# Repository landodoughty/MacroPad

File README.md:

# MacroPad
A Custom Macro Pad I Designed and Built based on the RP2040

# Features:
* Programmable keys allow shortcuts, macros, or controls to be customized.
* Hotswappable MX switches allows you to customize your typing feel.
* RGB Backlighting allows per-key lighting using WS2812/NeoPixel LEDs
* Custom 3d printed case provides a sleek, ergonomic look.

# Building the MacroPad

**The PCB:**
In this repository you can find the raw PCB files and the Gerber files which can allow you to manufacture the PCB through a service such as PCBWay or JLCPCB. I have also attached a BOM containing all the parts for the PCB. Most of the parts utilized on the PCB are very standard, and if you are assembling through JLCPCB the BOM already contains LCSC part numbers for most items. The only items which don't have part numbers, because I did not have them assembled through JLCPCB are the USB Micro-B connector, the reverse mount neopixel LEDs, the MX keyswitch sockets, and a small two pin 2.54mm pitch connector. The USB connector and the two pin connector can be easily bought from many places or even salvaged from old electronics. The [reverse mount LEDs]([url](https://www.adafruit.com/product/4960)) and [MX keyswitch sockets]([url](https://www.adafruit.com/product/4958)) are from adafruit. 

**Switches:**
You can use any MX compatible switches with the PCB, but keep in mind that they all have varying heights. The STLs provided are designed for switches with a 7mm above-board height with DSA keycaps, significantly less than most switches. If you want to use a different heigh you will likely have to adjust the STEP file provided to match your keyheight.

**Code:**
The code is provided but you will need to adjust it to fit your desires. This includes changing the LED modes and key press actions. Currently, the LED modes includes a constant color mode, an RGB mode, and a layer specific mode. To change layers, you press the first two buttons on the top row and then press the third button. To change colors in the constant color mode, you again press the first two buttons on the top row but then press the fourth button to change colors. To change the actions, scroll down to find the section where they are defined. The code shows how to do shortcuts, go to links, make a number pad, and how to create a shift key for a layer. To upload the code for the first time, short the two pins in the 2.54mm connector and then plug the MacroPad in through USB. It should pop up as detected and then yo ucan unshort the pins. Once you have done this once, you should be able to upload just with USB but if you are having issues uploading you may need to repeat the process.

**The Case:**
The case is 3d printed and I have provided both STL and STEP files for your conveinance. This means you can easily customize the case to your liking. The case needs 2 M3 heat set inserts, 2 M3 washers, and 2 M3 x 6 screws to assemble.

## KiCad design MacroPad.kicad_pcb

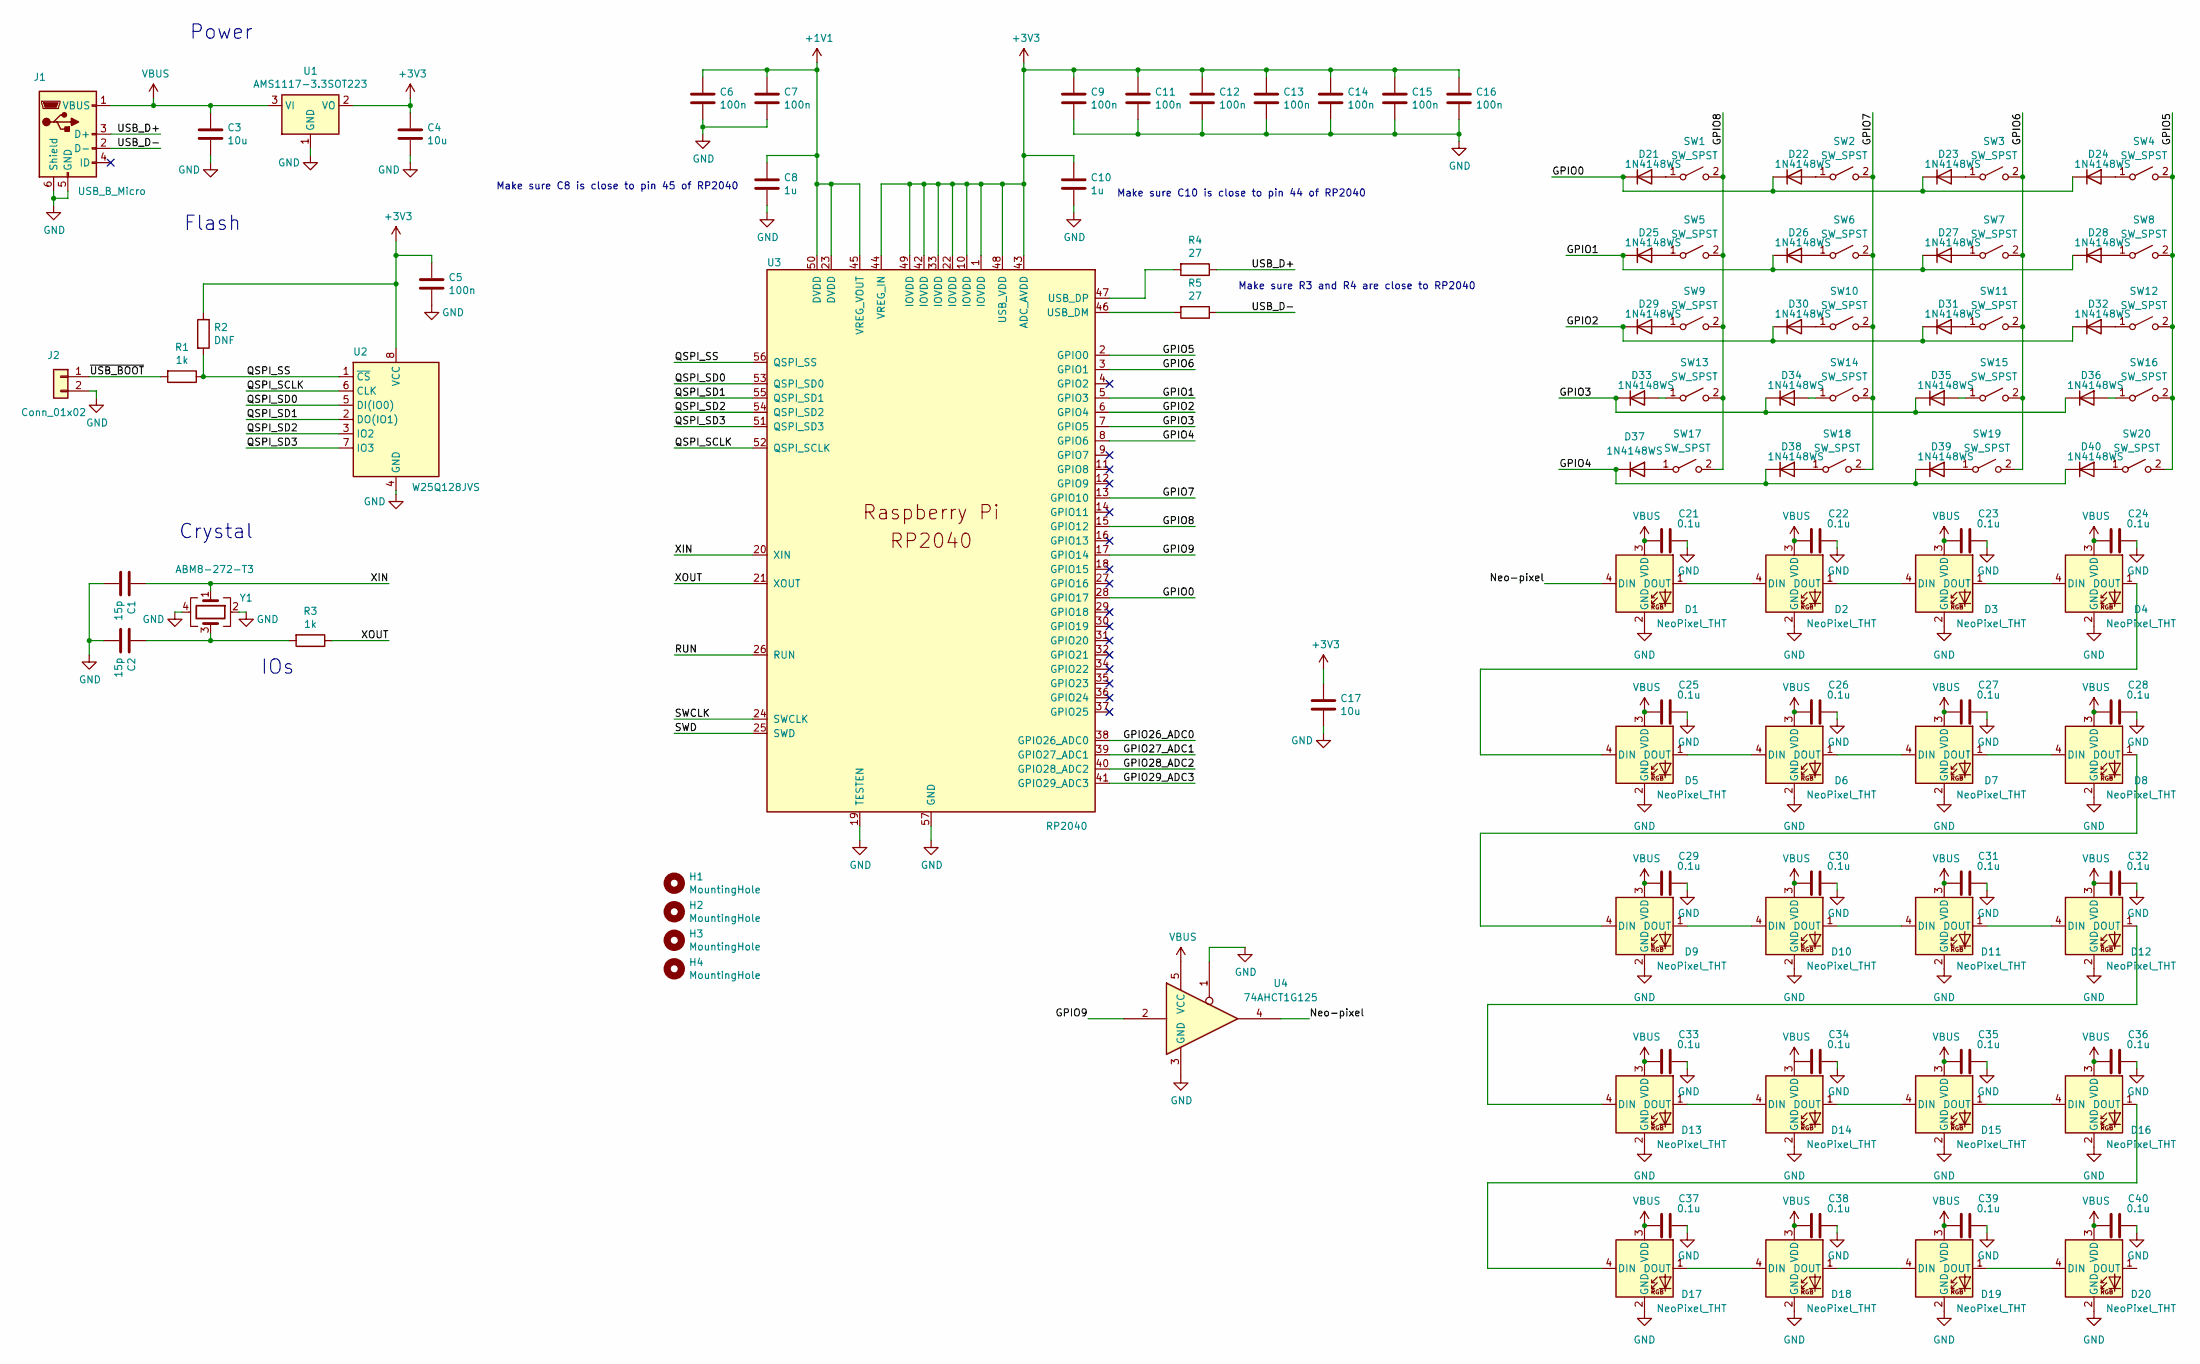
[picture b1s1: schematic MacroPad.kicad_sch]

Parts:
C1, C2: 15p; C_0603_1608Metric; LCSC Part Number C1644
C3, C4, C17: 10u; C_0805_2012Metric; LCSC Part Number C15850
C5, C6, C7, C9, C11, C12, C13, C14, C15, C16: 100n; C_0402_1005Metric; LCSC Part Number C1525
C8, C10: 1u; C_0402_1005Metric; LCSC Part Number C52923
C21, C22, C23, C24, C25, C26, C27, C28, C29, C30, C31, C32, C33, C34, C35, C36, C37, C38, C39, C40: 0.1u; C_0402_1005Metric; LCSC Part Number C1525
D1, D2, D3, D4, D5, D6, D7, D8, D9, D10, D11, D12, D13, D14, D15, D16, D17, D18, D19, D20: NeoPixel_THT; NEO3535_REVERSECorrected
D21, D22, D23, D24, D25, D26, D27, D28, D29, D30, D31, D32, D33, D34, D35, D36, D37, D38, D39, D40: 1N4148WS; D_SOD-323; LCSC Part Number C2128
H1, H2, H3, H4: MountingHole; MountingHole_3.2mm_M3_ISO14580_Pad
J1: USB_B_Micro; USB_Micro-B_Amphenol_10103594-0001LF_Horizontal; LCSC Part Number C10418
J2: Conn_01x02; PinHeader_1x02_P2.54mm_Vertical
R1, R3: 1k; R_0402_1005Metric; LCSC Part Number C11702
R2: DNF; R_0402_1005Metric
R4, R5: 27; R_0402_1005Metric; LCSC Part Number C25100
SW1, SW2, SW3, SW4, SW5, SW6, SW7, SW8, SW9, SW10, SW11, SW12, SW13, SW14, SW15, SW16, SW17, SW18, SW19, SW20: SW_SPST; Kailh_socket_MX
U1: AMS1117-3.3SOT223; SOT-223; LCSC Part Number C6186
U2: W25Q128JVS; SOIC-8_5.23x5.23mm_P1.27mm; LCSC Part Number C97521
U3: RP2040; QFN-56-1EP_7x7mm_P0.4mm_EP3.2x3.2mm; LCSC Part Number C2040
U4: 74AHCT1G125; SOT-23-5; LCSC Part Number C7484
Y1: ABM8-272-T3; Crystal_SMD_3225-4Pin_3.2x2.5mm; LCSC Part Number C20625731

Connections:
+1V1: C6.1, C7.1, C8.1, U3.23 (DVDD), U3.45 (VREG_VOUT), U3.50 (DVDD)
+3V3: C4.1, C5.1, C9.1, C10.1, C11.1, C12.1, C13.1, C14.1, C15.1, C16.1, C17.1, R2.1, U1.2 (VO), U2.8 (VCC), U3.1 (IOVDD), U3.10 (IOVDD), U3.22 (IOVDD), U3.33 (IOVDD), U3.42 (IOVDD), U3.43 (ADC_AVDD), U3.44 (VREG_IN), U3.48 (USB_VDD), U3.49 (IOVDD)
/GPIO0: D21.1 (K), D22.1 (K), D23.1 (K), D24.1 (K), U3.28 (GPIO17)
/GPIO1: D25.1 (K), D26.1 (K), D27.1 (K), D28.1 (K), U3.5 (GPIO3)
/GPIO2: D29.1 (K), D30.1 (K), D31.1 (K), D32.1 (K), U3.6 (GPIO4)
/GPIO3: D33.1 (K), D34.1 (K), D35.1 (K), D36.1 (K), U3.7 (GPIO5)
/GPIO4: D37.1 (K), D38.1 (K), D39.1 (K), D40.1 (K), U3.8 (GPIO6)
/GPIO5: SW4.2 (B), SW8.2 (B), SW12.2 (B), SW16.2 (B), SW20.2 (B), U3.2 (GPIO0)
/GPIO6: SW3.2 (B), SW7.2 (B), SW11.2 (B), SW15.2 (B), SW19.2 (B), U3.3 (GPIO1)
/GPIO7: SW2.2 (B), SW6.2 (B), SW10.2 (B), SW14.2 (B), SW18.2 (B), U3.13 (GPIO10)
/GPIO8: SW1.2 (B), SW5.2 (B), SW9.2 (B), SW13.2 (B), SW17.2 (B), U3.15 (GPIO12)
/GPIO9: U3.17 (GPIO14), U4.2
/GPIO26_ADC0: U3.38 (GPIO26_ADC0)
/GPIO27_ADC1: U3.39 (GPIO27_ADC1)
/GPIO28_ADC2: U3.40 (GPIO28_ADC2)
/GPIO29_ADC3: U3.41 (GPIO29_ADC3)
/Neo-pixel: D1.4 (DIN), U4.4
/QSPI_SCLK: U2.6 (CLK), U3.52 (QSPI_SCLK)
/QSPI_SD0: U2.5 (DI(IO0)), U3.53 (QSPI_SD0)
/QSPI_SD1: U2.2 (DO(IO1)), U3.55 (QSPI_SD1)
/QSPI_SD2: U2.3 (IO2), U3.54 (QSPI_SD2)
/QSPI_SD3: U2.7 (IO3), U3.51 (QSPI_SD3)
/QSPI_SS: R1.1, R2.2, U2.1 (~CS), U3.56 (QSPI_SS)
/RUN: U3.26 (RUN)
/SWCLK: U3.24 (SWCLK)
/SWD: U3.25 (SWD)
/USB_D+: J1.3 (D+), R4.1
/USB_D-: J1.2 (D-), R5.1
/XIN: C1.1, U3.20 (XIN), Y1.1
/XOUT: R3.1, U3.21 (XOUT)
/~USB_BOOT: J2.1, R1.2
GND: C1.2, C2.2, C3.2, C4.2, C5.2, C6.2, C7.2, C8.2, C9.2, C10.2, C11.2, C12.2, C13.2, C14.2, C15.2, C16.2, C17.2, C21.2, C22.2, C23.2, C24.2, C25.2, C26.2, C27.2, C28.2, C29.2, C30.2, C31.2, C32.2, C33.2, C34.2, C35.2, C36.2, C37.2, C38.2, C39.2, C40.2, D1.2 (GND), D2.2 (GND), D3.2 (GND), D4.2 (GND), D5.2 (GND), D6.2 (GND), D7.2 (GND), D8.2 (GND), D9.2 (GND), D10.2 (GND), D11.2 (GND), D12.2 (GND), D13.2 (GND), D14.2 (GND), D15.2 (GND), D16.2 (GND), D17.2 (GND), D18.2 (GND), D19.2 (GND), D20.2 (GND), J1.5 (GND), J1.6 (Shield), J2.2, U1.1 (GND), U2.4 (GND), U3.19 (TESTEN), U3.57 (GND), U4.1, U4.3 (GND), Y1.2, Y1.4
unnamed: C2.1, R3.2, Y1.3
unnamed: D1.1 (DOUT), D2.4 (DIN)
unnamed: D2.1 (DOUT), D3.4 (DIN)
unnamed: D3.1 (DOUT), D4.4 (DIN)
unnamed: D4.1 (DOUT), D5.4 (DIN)
unnamed: D5.1 (DOUT), D6.4 (DIN)
unnamed: D6.1 (DOUT), D7.4 (DIN)
unnamed: D7.1 (DOUT), D8.4 (DIN)
unnamed: D8.1 (DOUT), D9.4 (DIN)
unnamed: D9.1 (DOUT), D10.4 (DIN)
unnamed: D10.1 (DOUT), D11.4 (DIN)
unnamed: D11.1 (DOUT), D12.4 (DIN)
unnamed: D12.1 (DOUT), D13.4 (DIN)
unnamed: D13.1 (DOUT), D14.4 (DIN)
unnamed: D14.1 (DOUT), D15.4 (DIN)
unnamed: D15.1 (DOUT), D16.4 (DIN)
unnamed: D16.1 (DOUT), D17.4 (DIN)
unnamed: D17.1 (DOUT), D18.4 (DIN)
unnamed: D18.1 (DOUT), D19.4 (DIN)
unnamed: D19.1 (DOUT), D20.4 (DIN)
unnamed: D21.2 (A), SW1.1 (A)
unnamed: D22.2 (A), SW2.1 (A)
unnamed: D23.2 (A), SW3.1 (A)
unnamed: D24.2 (A), SW4.1 (A)
unnamed: D25.2 (A), SW5.1 (A)
unnamed: D26.2 (A), SW6.1 (A)
unnamed: D27.2 (A), SW7.1 (A)
unnamed: D28.2 (A), SW8.1 (A)
unnamed: D29.2 (A), SW9.1 (A)
unnamed: D30.2 (A), SW10.1 (A)
unnamed: D31.2 (A), SW11.1 (A)
unnamed: D32.2 (A), SW12.1 (A)
unnamed: D33.2 (A), SW13.1 (A)
unnamed: D34.2 (A), SW14.1 (A)
unnamed: D35.2 (A), SW15.1 (A)
unnamed: D36.2 (A), SW16.1 (A)
unnamed: D37.2 (A), SW17.1 (A)
unnamed: D38.2 (A), SW18.1 (A)
unnamed: D39.2 (A), SW19.1 (A)
unnamed: D40.2 (A), SW20.1 (A)
unnamed: R5.2, U3.46 (USB_DM)
unnamed: R4.2, U3.47 (USB_DP)
VBUS: C3.1, C21.1, C22.1, C23.1, C24.1, C25.1, C26.1, C27.1, C28.1, C29.1, C30.1, C31.1, C32.1, C33.1, C35.1, C36.1, C37.1, C38.1, C39.1, C40.1, D1.3 (VDD), D2.3 (VDD), D3.3 (VDD), D4.3 (VDD), D5.3 (VDD), D6.3 (VDD), D7.3 (VDD), D8.3 (VDD), D9.3 (VDD), D10.3 (VDD), D11.3 (VDD), D12.3 (VDD), D13.3 (VDD), D14.3 (VDD), D15.3 (VDD), D16.3 (VDD), D17.3 (VDD), D18.3 (VDD), D19.3 (VDD), D20.3 (VDD), J1.1 (VBUS), U1.3 (VI), U4.5 (VCC)

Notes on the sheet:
IOs
Make sure R3 and R4 are close to RP2040
Make sure C10 is close to pin 44 of RP2040
Make sure C8 is close to pin 45 of RP2040
Power
Crystal
Flash

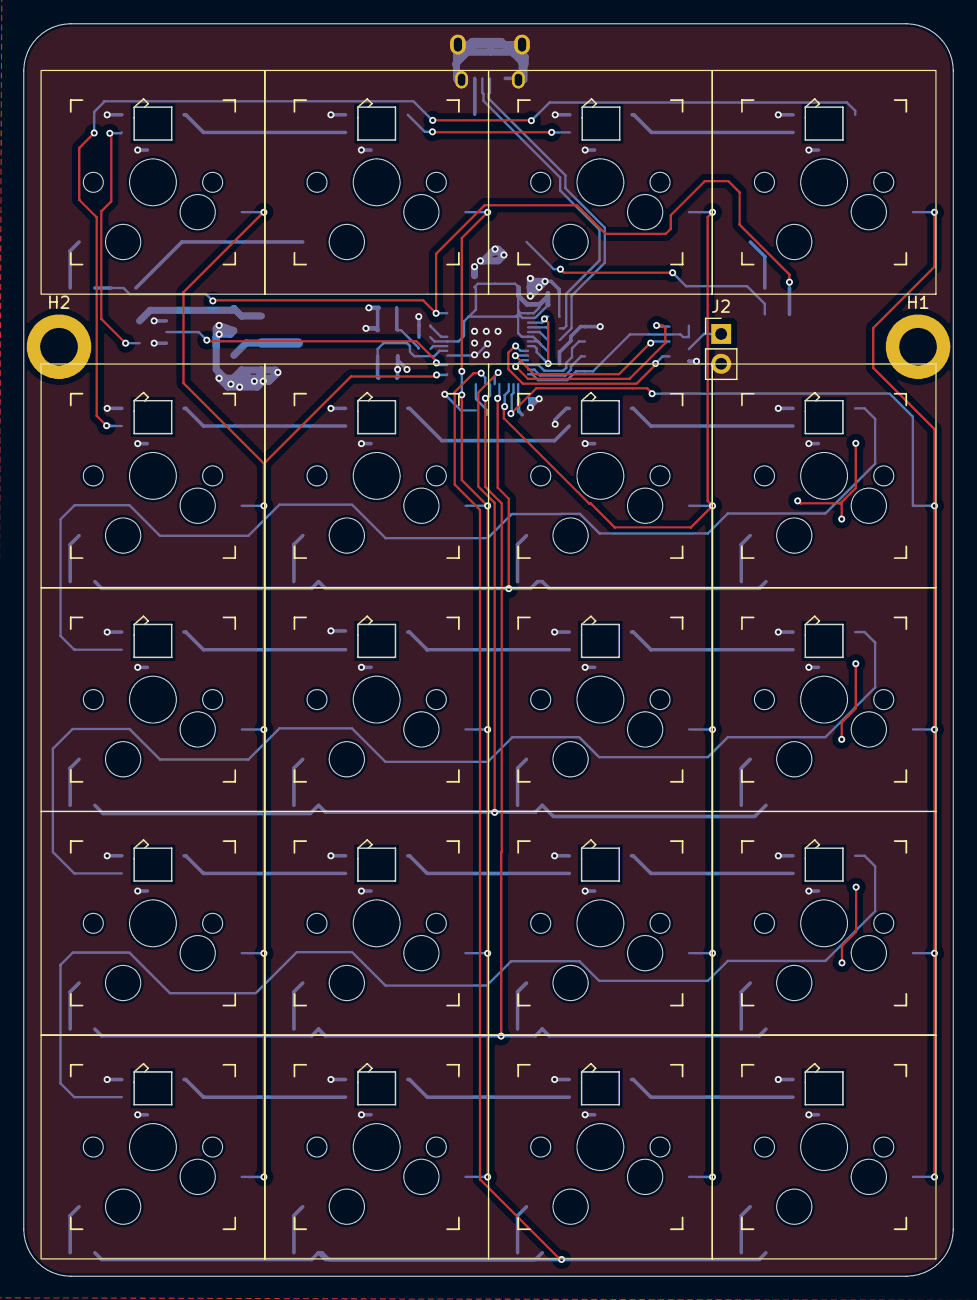
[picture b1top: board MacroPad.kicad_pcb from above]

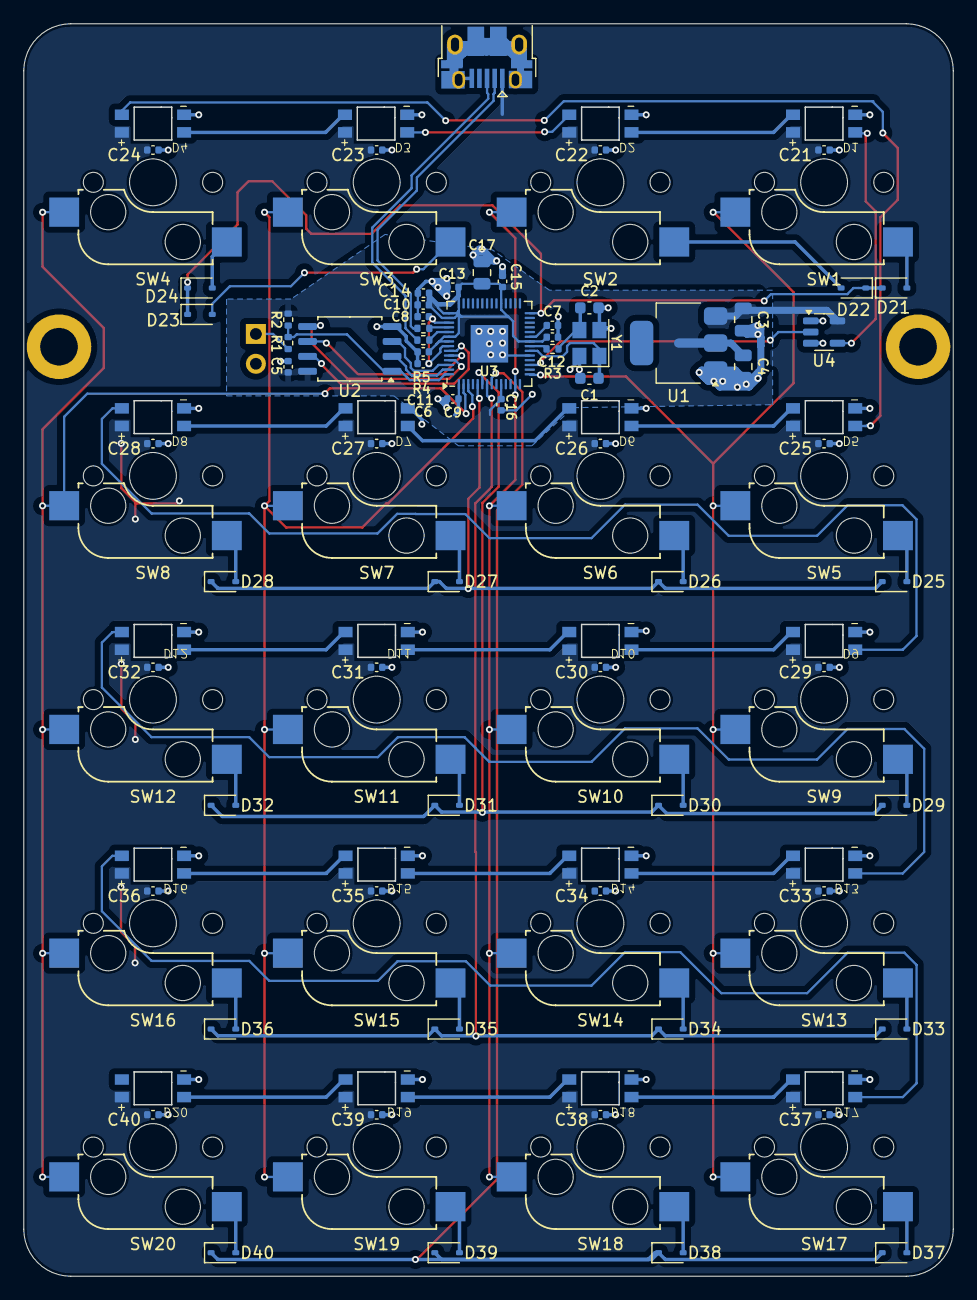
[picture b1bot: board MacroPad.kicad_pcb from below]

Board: 2 copper layers, 79.2 x 106.7 mm, 111 parts (68 on the bottom side), 68 nets.

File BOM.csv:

"Designator","Comment","Datasheet","Footprint","LCSC Part Number","Qty","DNP"
"C1,C2","15p","~","Capacitor_SMD:C_0603_1608Metric","C1644","2",""
"C3,C4,C17","10u","~","Capacitor_SMD:C_0805_2012Metric","C15850","3",""
"C5,C6,C7,C9,C11,C12,C13,C14,C15,C16","100n","~","Capacitor_SMD:C_0402_1005Metric","C1525","10",""
"C8,C10","1u","~","Capacitor_SMD:C_0402_1005Metric","C52923","2",""
"C21,C22,C23,C24,C25,C26,C27,C28,C29,C30,C31,C32,C33,C34,C35,C36,C37,C38,C39,C40","0.1u","~","Capacitor_SMD:C_0402_1005Metric","C1525","20",""
"D1,D2,D3,D4,D5,D6,D7,D8,D9,D10,D11,D12,D13,D14,D15,D16,D17,D18,D19,D20","NeoPixel_THT","https://www.adafruit.com/product/1938","neoPixel:NEO3535_REVERSECorrected","","20",""
"D21,D22,D23,D24,D25,D26,D27,D28,D29,D30,D31,D32,D33,D34,D35,D36,D37,D38,D39,D40","1N4148WS","https://www.vishay.com/docs/85751/1n4148ws.pdf","Diode_SMD:D_SOD-323"," C2128","20",""
"H1,H2,H3,H4","MountingHole","~","MountingHole:MountingHole_3.2mm_M3_ISO14580_Pad","","4",""
"J1","USB_B_Micro","~","Connector_USB:USB_Micro-B_Amphenol_10103594-0001LF_Horizontal","C10418","1",""
"J2","Conn_01x02","~","Connector_PinHeader_2.54mm:PinHeader_1x02_P2.54mm_Vertical","","1",""
"R1,R3","1k","~","Resistor_SMD:R_0402_1005Metric","C11702","2",""
"R2","DNF","~","Resistor_SMD:R_0402_1005Metric","","1",""
"R4,R5","27","~","Resistor_SMD:R_0402_1005Metric","C25100","2",""
"SW1,SW2,SW3,SW4,SW5,SW6,SW7,SW8,SW9,SW10,SW11,SW12,SW13,SW14,SW15,SW16,SW17,SW18,SW19,SW20","SW_SPST","~","keyswitches:Kailh_socket_MX","","20",""
"U1","AMS1117-3.3SOT223","http://www.advanced-monolithic.com/pdf/ds1117.pdf","Package_TO_SOT_SMD:SOT-223","C6186","1",""
"U2","W25Q128JVS","http://www.winbond.com/resource-files/w25q128jv_dtr%20revc%2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","Package_SO:SOIC-8_5.23x5.23mm_P1.27mm","C97521","1",""
"U3","RP2040","","Package_DFN_QFN:QFN-56-1EP_7x7mm_P0.4mm_EP3.2x3.2mm","C2040","1",""
"U4","74AHCT1G125","http://www.ti.com/lit/sg/scyt129e/scyt129e.pdf","Package_TO_SOT_SMD:SOT-23-5","C7484","1",""
"Y1","ABM8-272-T3","~","Crystal:Crystal_SMD_3225-4Pin_3.2x2.5mm","C20625731","1",""

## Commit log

2025-06-26 Custom PCB files
    BOM and CSV adjusted for JLCPCB assembly
2025-07-03 Basic Customizable Code
2025-07-03 CAD Files
2025-07-05 STEP Files
